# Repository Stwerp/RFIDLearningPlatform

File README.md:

# RFIDLearningPlatform
Open-source platform for RFID experimentation. Build your own battery-free device

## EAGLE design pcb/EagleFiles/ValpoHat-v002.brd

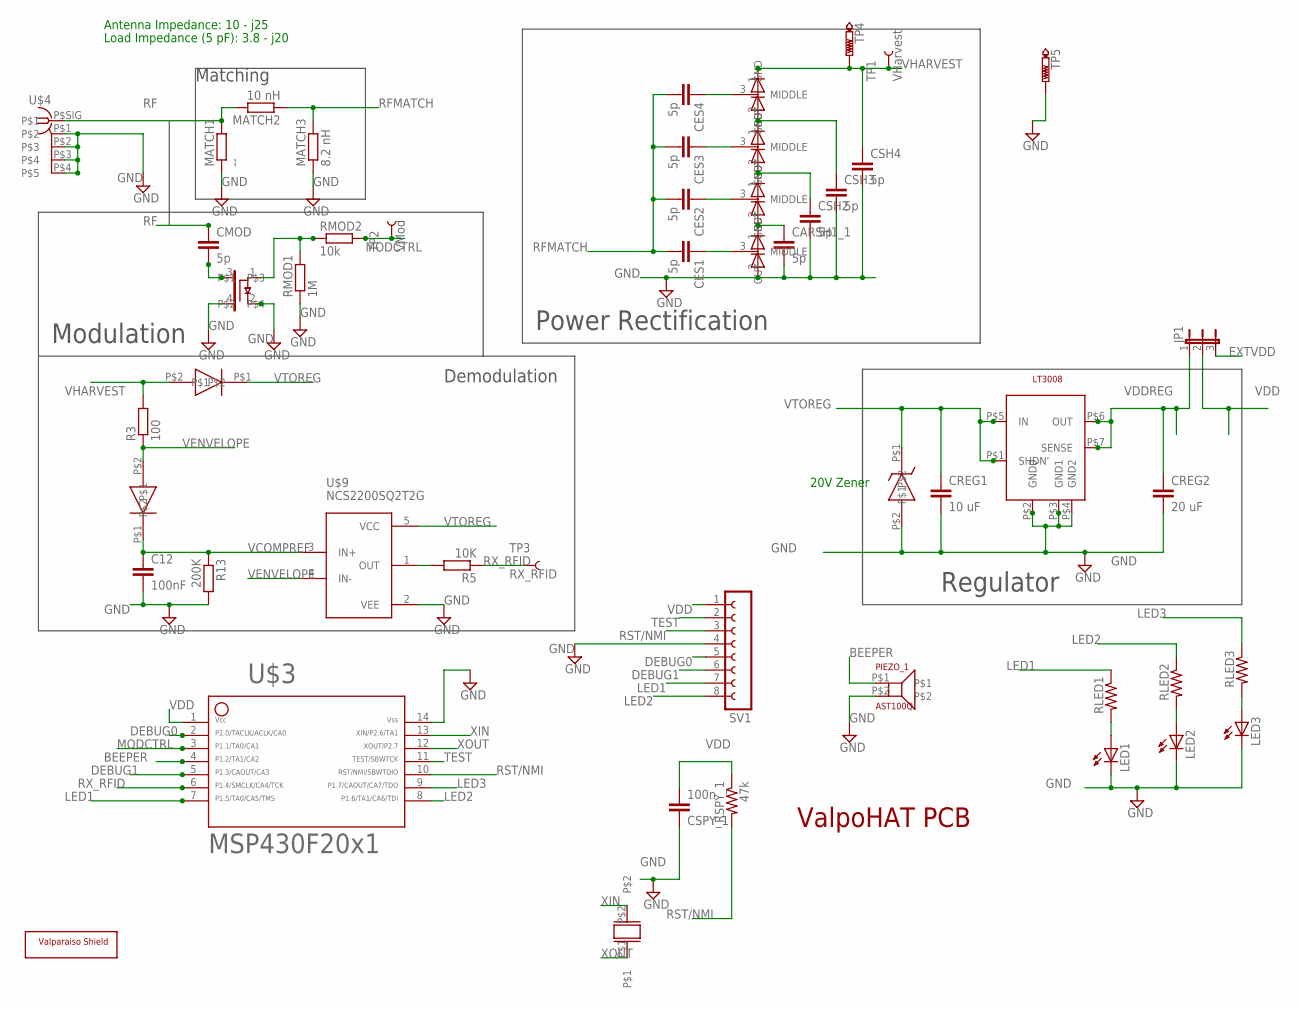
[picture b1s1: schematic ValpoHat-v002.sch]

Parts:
C12: 100nF; C1206
CARSH1_1: 5p; C0603
CES1, CES2, CES3, CES4: 5p; C0603
CMOD: 5p; C0603
CREG1: 10 uF; C1206
CREG2: 20 uF; C1206
CSH2, CSH3, CSH4: 5p; C0603
CSPY_1: 100n; C1206
D1, D2: RB751S40T1_EXPAND; SOD-523_EXPAND
JP1: JP2E; JP2
LED1, LED2, LED3: LEDCHIP-LED0603; CHIP-LED0603
MATCH1: --; R0603
MATCH2: 10 nH; R0603
MATCH3: 8.2 nH; R0603
PIEZO_1: AST100Q
R3: 100; R1206
R5: 10K; R1206
R13: 200K; R1206
RLED1, RLED2, RLED3: R-US_R1206; R1206
RMOD1: 1M; R1206
RMOD2: 10k; R1206
RSPY_1: 47k; R1206
SV1: FE08-1; FE08
TP1: VHarvest; PAD.03X.03
TP2: VMod; PAD.03X.03
TP3: RX_RFID; PAD.03X.03
TP4, TP5: TESTPAD_PTR1PAD1-13; TESTPAD_P1-13
U$1: BF1108R; SOT-143R
U$2: MMSZ4707T1; SOD-123
U$3: F20X1---N14; N14
U$4: SMA_EDGE_CONN_ALT; SMA_EDGE_2SIDE
U$5, U$6, U$7, U$8: HSMS2852; SOT23
U$9: NCS2200SQ2T2G; SC70-5
U$10: LT3008-TSOT; TSOT-23
U$11: VALPARAISO-SHIELD; VUSHIELD-200MIL
UCRY_1: ECX31-BSOLDERABLE; ECX31-B_EXPAND

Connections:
BEEPER: PIEZO_1.P$1, U$3.4
DEBUG0: SV1.5, U$3.2
DEBUG1: SV1.6, U$3.5
EXTVDD: JP1.3
GND: C12.2, CARSH1_1.2, CREG1.2, CREG2.2, CSH2.2, CSH3.2, CSH4.2, CSPY_1.1, LED1.C, LED2.C, LED3.C, MATCH1.1, MATCH3.1, PIEZO_1.P$2, R13.2, RMOD1.1, SV1.4, TP5.TP, U$1.2, U$1.4, U$2.P$2, U$3.14, U$4.P$1, U$4.P$2, U$4.P$3, U$4.P$4, U$5.2 (GND), U$9.2 (VEE), U$10.P$2 (GND0), U$10.P$3 (GND1), U$10.P$4 (GND2)
LED1: RLED1.1, SV1.7, U$3.7
LED2: RLED2.1, SV1.8, U$3.8
LED3: RLED3.1, U$3.9
MODCTRL: RMOD2.2, TP2.P$1, U$3.3
unnamed: CMOD.2, U$1.3
unnamed: RMOD1.2, RMOD2.1, U$1.1
unnamed: LED3.A, RLED3.2
unnamed: CARSH1_1.1, U$5.1 (OUT), U$6.2 (GND)
unnamed: LED1.A, RLED1.2
unnamed: LED2.A, RLED2.2
unnamed: CES2.1, U$6.3 (MIDDLE)
unnamed: CES1.1, U$5.3 (MIDDLE)
unnamed: R5.2, U$9.1 (OUT)
unnamed: CSH2.1, U$6.1 (OUT), U$7.2 (GND)
unnamed: CSH3.1, U$7.1 (OUT), U$8.2 (GND)
unnamed: CES4.1, U$8.3 (MIDDLE)
unnamed: CES3.1, U$7.3 (MIDDLE)
RF: CMOD.1, MATCH1.2, MATCH2.2, U$4.P$SIG
RFMATCH: CES1.2, CES2.2, CES3.2, CES4.2, MATCH2.1, MATCH3.2
RST/NMI: RSPY_1.2, SV1.3, U$3.10
RX_RFID: R5.1, TP3.P$1, U$3.6
TEST: SV1.2, U$3.11
VCOMPREF: C12.1, D2.P$1, R13.1, U$9.3 (IN+)
VDD: CSPY_1.2, JP1.2, RSPY_1.1, SV1.1, U$3.1
VDDREG: CREG2.1, JP1.1, U$10.P$6 (OUT), U$10.P$7 (SENSE)
VENVELOPE: D2.P$2, R3.1, U$9.4 (IN-)
VHARVEST: CSH4.1, D1.P$2, R3.2, TP1.P$1, TP4.TP, U$8.1 (OUT)
VTOREG: CREG1.1, D1.P$1, U$2.P$1, U$9.5 (VCC), U$10.P$1 (SHDN'), U$10.P$5 (IN)
XIN: U$3.13, UCRY_1.P$2
XOUT: U$3.12, UCRY_1.P$1

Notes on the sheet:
ValpoHAT PCB
Modulation
Matching
Power Rectification
Regulator
Antenna Impedance: 10 - j25
Load Impedance (5 pF): 3.8 - j20
20V Zener
Demodulation

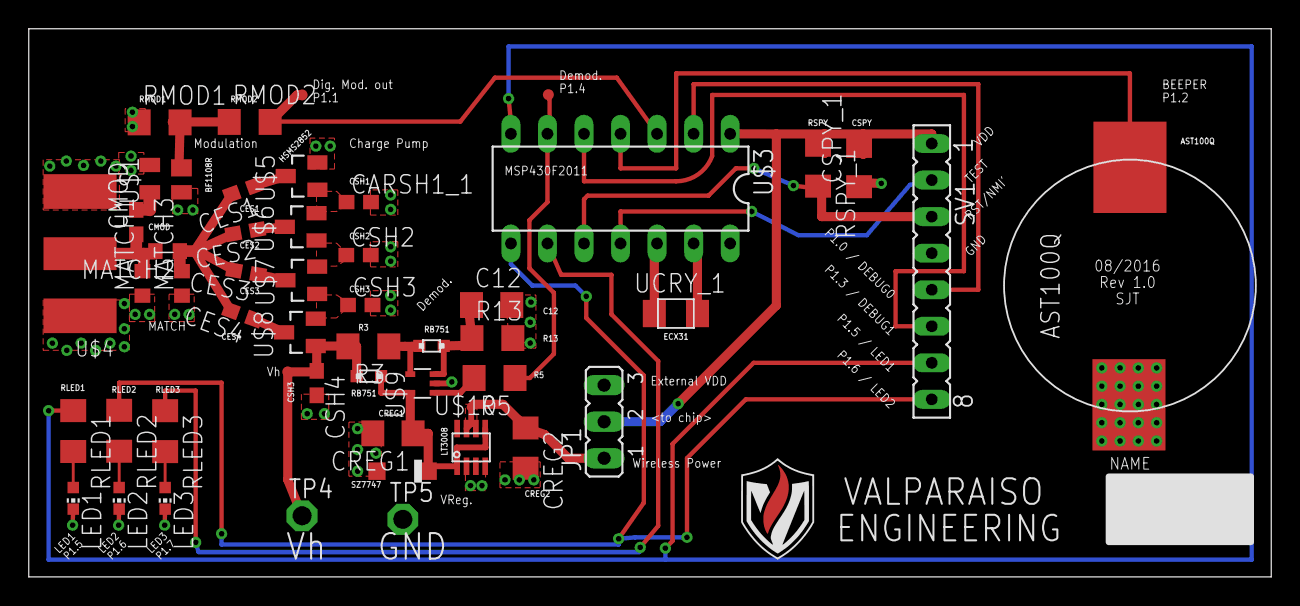
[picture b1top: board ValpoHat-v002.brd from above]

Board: 2 copper layers, 86.4 x 38.1 mm, 50 parts (0 on the bottom side), 34 nets.

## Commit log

2019-04-01 adds lecture nots
2019-04-01 adds sylabus
2019-04-01 ignore file
2019-04-01 Adds homework binaries
2019-04-01 Adds support scripts and BOM
2019-04-01 adds list of software used in the course
2019-04-02 reverts to textfile
2019-04-02 updates csv cell breaks
